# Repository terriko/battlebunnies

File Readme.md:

# Battle bunnies!

This is a goofy little side project that involves making a little electronic
bunny game in the name of learning a bit more about electronic badge design.

## How the game is played

Battle bunnies is meant to be a simple electronic game.  Each participant
gets their own bunny.  The bunnies have IR on one side of the PCB.
Participants line up their IR with the IR of another bunny and both hit the
"fight" button.  The bunnies each "roll" a random number 1-6 which is shown
on one ear and transmit that number to the other bunny.  The bunny with the
highest number gains a level.  In the case of a tie, both bunnies gain a
level (because why not?).  The levels are updated on the other ear.
Depending on how slow we want the level process to be, losing bunnies might
lose a level.

The "magic" button is an easter egg that can be activated when bunnies reach
max level.

## Bunny design

These are all early drafts which I'm sure we'll change.

### PCB outline

### Silkscreen bunny

### Explanation of what components go where

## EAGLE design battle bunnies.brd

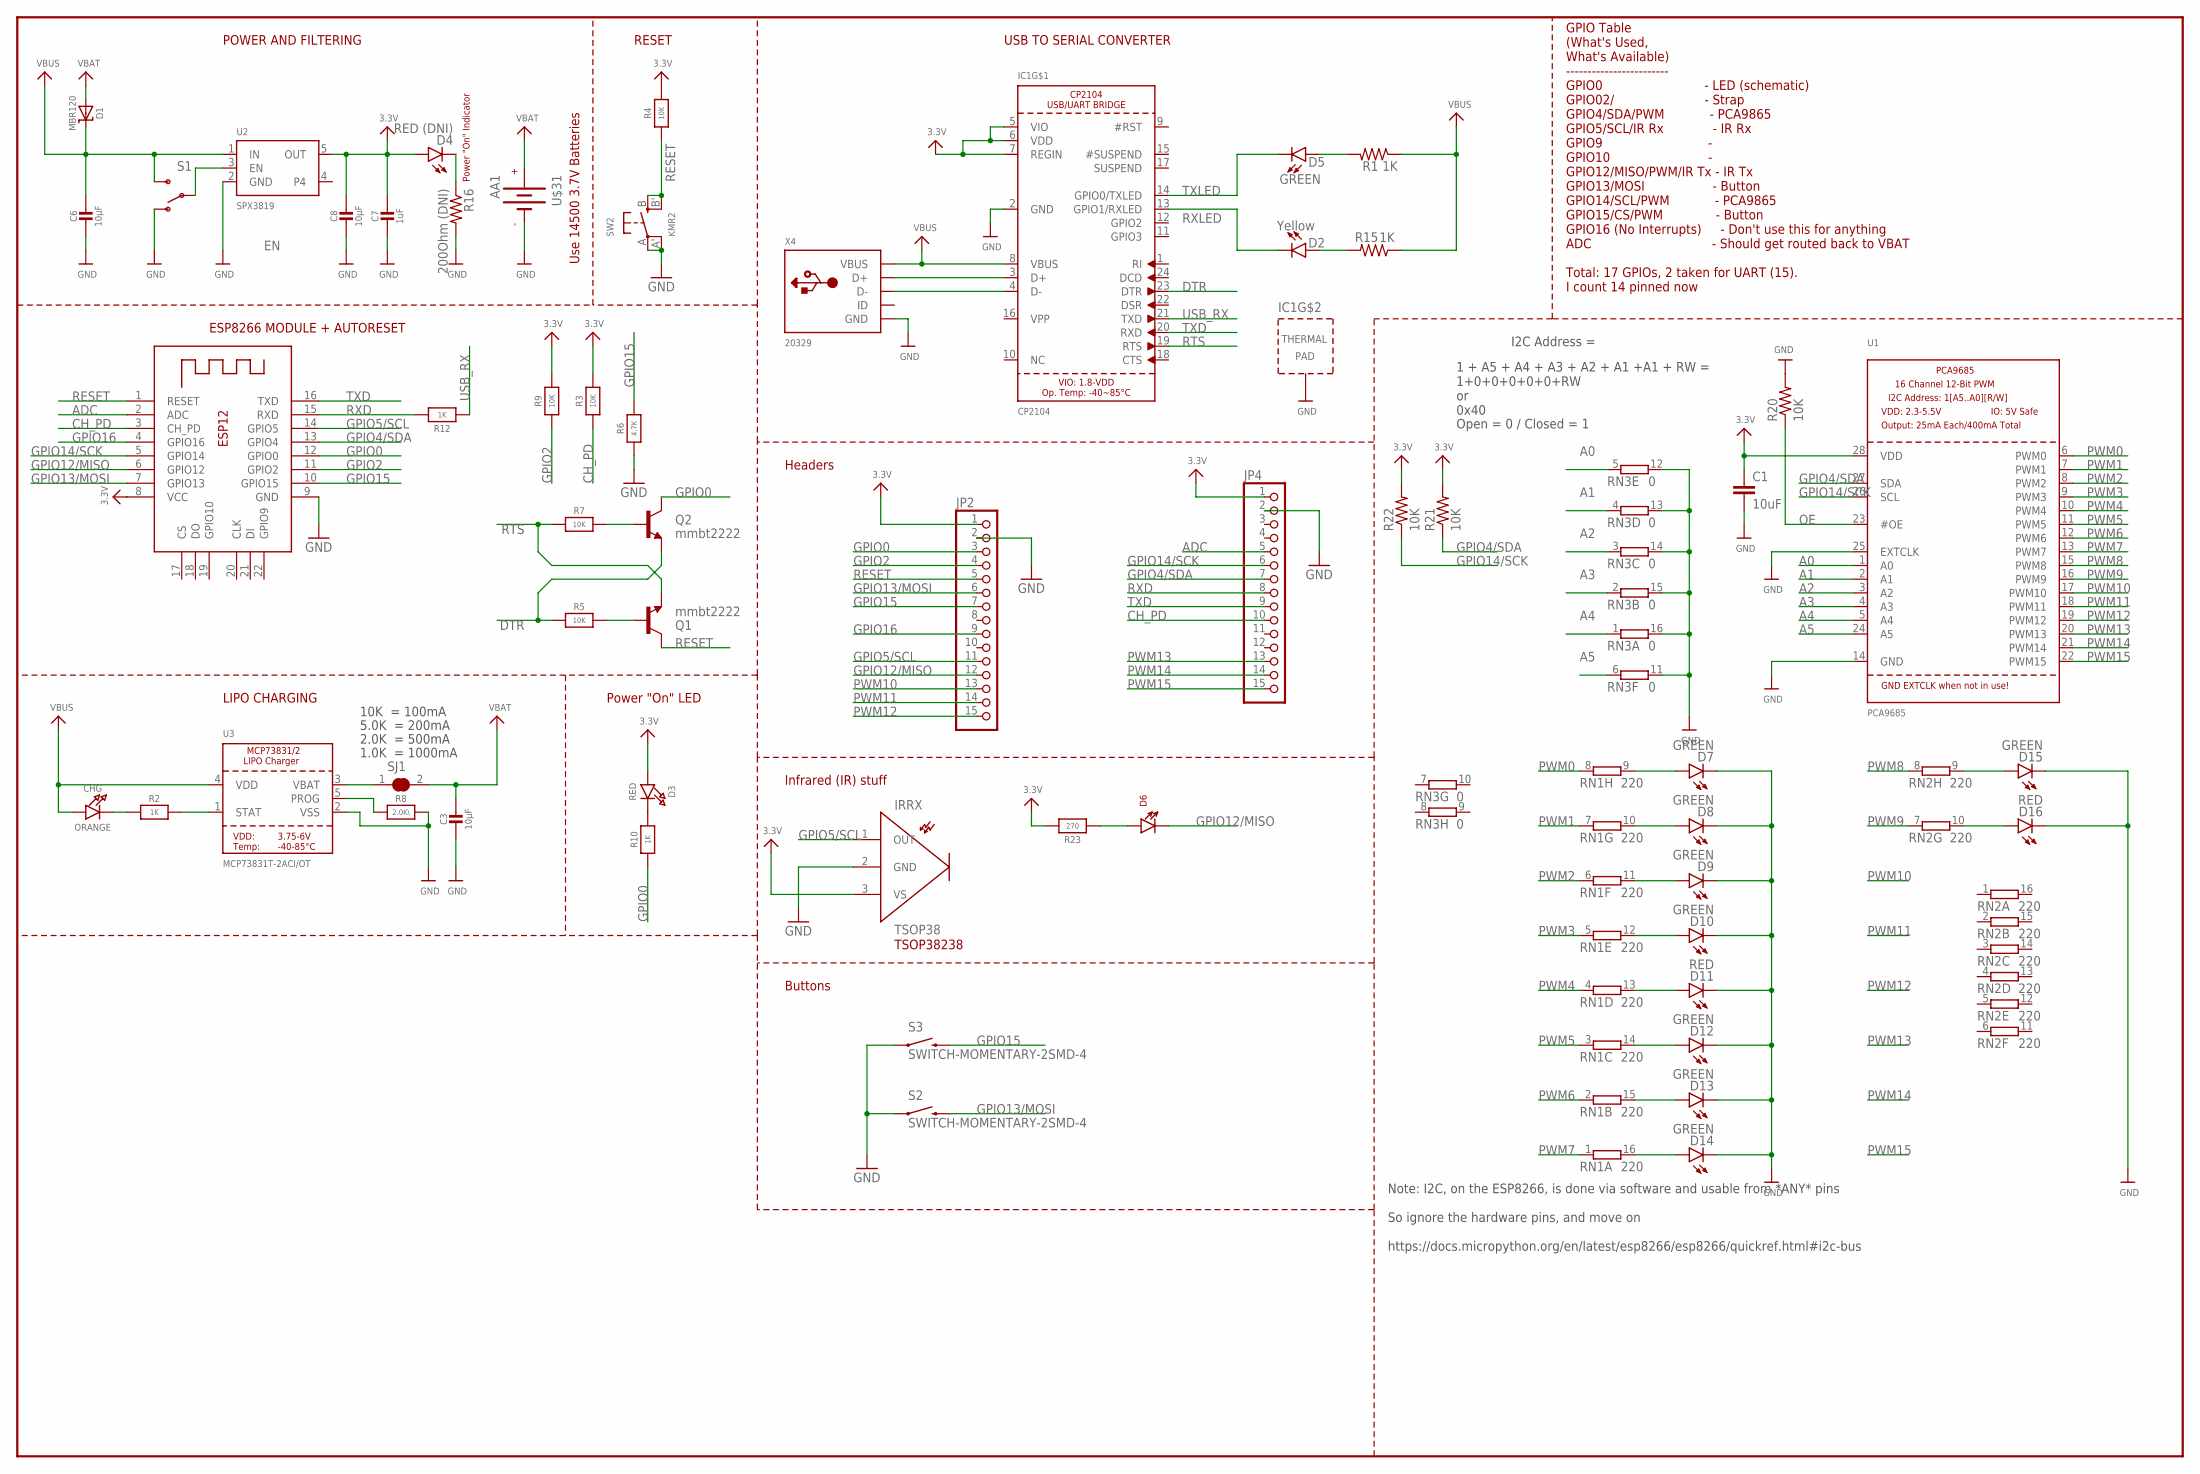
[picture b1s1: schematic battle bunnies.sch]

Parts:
C1: 10uF; 0805-CAP
C3, C6, C8: 10µF; 0805-NO
C7: 1uF; 0603-NO
CHG: ORANGE; CHIPLED_0805_NOOUTLINE
D1: MBR120; SOD-123
D2: Yellow; LED-0603
D3: RED; CHIPLED_0805_NOOUTLINE
D4: RED (DNI); LED-0603
D5, D7, D8, D9, D10, D12, D13, D14, D15: GREEN; LED-0603
D6: LTE-302
D11, D16: RED; LED-0603
IC1: CP2104; QFN24_4MM_SMSC
IRRX: TSOP38
JP2, JP4: PINHD-1X15; 1X15
Q1, Q2: mmbt2222; SOT23-3
R1, R15: 1K; 0603-RES
R2, R10: 1K; 0603-NO
R3, R4, R5, R9: 10K; 0603-NO
R6: 4.7K; 0603-NO
R7: 10K; _0603MP
R8: 2.0K\; 0603-NO
R12: 1K; _0603MP
R16: 200Ohm (DNI); 0603-RES
R20, R21, R22: 10K; 0805
R23: 270; 0603-NO
RN1, RN2: 220; EXB2HV
RN3: 0; EXB2HV
S1: SWITCH-SPDT-SMD-A; SWITCH-SPST-SMD-A
S2, S3: SWITCH-MOMENTARY-2SMD-4; TACTILE_SWITCH_TALL
SJ1: SOLDERJUMPER_CLOSED; SOLDERJUMPER_CLOSEDWIRE@1
SW2: KMR2; BTN_KMR2_4.6X2.8
U1: PCA9685; TSSOP28
U2: SPX3819; SOT23-5
U3: MCP73831T-2ACI/OT; SOT23-5
U$31: AA1
X2: ESP-12; ESP-12E
X4: 20329; 4UCONN_20329_V2

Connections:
3.3V: C1.1, C7.1, C8.1, D3.A, D4.A, IC1.5 (VIO), IC1.6 (VDD), IC1.7 (REGIN), IRRX.3 (VS), JP2.1, JP4.1, R1.1, R3.2, R4.2, R9.2, R15.1, R21.2, R22.2, R23.2, U1.28 (VDD), U2.5 (OUT), X2.8 (VCC)
A0: RN3.5 (1), U1.1 (A0)
A1: RN3.4 (1), U1.2 (A1)
A2: RN3.3 (1), U1.3 (A2)
A3: RN3.2 (1), U1.4 (A3)
A4: RN3.1, U1.5 (A4)
A5: RN3.6 (1), U1.24 (A5)
ADC: JP4.5, X2.2 (ADC)
CH_PD: JP4.10, R3.1, X2.3 (CH_PD)
DTR: IC1.23 (DTR), Q2.2 (E), R5.1
EN: S1.2, U2.3 (EN)
GND: C1.2, C3.2, C6.2, C7.2, C8.2, D7.C, D8.C, D9.C, D10.C, D11.C, D12.C, D13.C, D14.C, D15.C, D16.C, IC1.2 (GND), IC1.THERM (TP), IRRX.2 (GND), JP2.2, JP4.2, R6.1, R8.2, R16.2, R20.2, RN3.11 (2), RN3.12 (2), RN3.13 (2), RN3.14 (2), RN3.15 (2), RN3.16 (2), S1.1 (O), S2.A2 (1), S3.A2 (1), SW2.A, SW2.A' (P1), U1.14 (GND), U1.25 (EXTCLK), U2.2 (GND), U3.2 (VSS), U$31.NEG (-), X2.9 (GND), X4.BASE@1 (GND), X4.BASE@2 (GND), X4.GND, X4.SPRT@1 (GND), X4.SPRT@2 (GND), X4.SPRT@3 (GND), X4.SPRT@4 (GND)
GPIO0: JP2.3, Q2.3 (C), R10.1, X2.12 (GPIO0)
GPIO2: JP2.4, R9.1, X2.11 (GPIO2)
GPIO4/SDA: JP4.7, R21.1, U1.27 (SDA), X2.13 (GPIO4)
GPIO5/SCL: IRRX.1 (OUT), JP2.11, X2.14 (GPIO5)
GPIO12/MISO: D6.C, JP2.12, X2.6 (GPIO12)
GPIO13/MOSI: JP2.6, S2.B2 (2), X2.7 (GPIO13)
GPIO14/SCK: JP4.6, R22.1, U1.26 (SCL), X2.5 (GPIO14)
GPIO15: JP2.7, R6.2, S3.B2 (2), X2.10 (GPIO15)
GPIO16: JP2.9, X2.4 (GPIO16)
unnamed: CHG.C, R2.1
unnamed: R8.1, U3.5 (PROG)
unnamed: R2.2, U3.1 (STAT)
unnamed: D4.C, R16.1
unnamed: D3.C, R10.2
unnamed: D5.A, R1.2
unnamed: SJ1.1, U3.3 (VBAT)
unnamed: D2.A, R15.2
unnamed: Q1.1 (B), R5.2
unnamed: Q2.1 (B), R7.2
unnamed: D6.A, R23.1
unnamed: D13.A, RN1.15 (2)
unnamed: D14.A, RN1.16 (2)
unnamed: D12.A, RN1.14 (2)
unnamed: D11.A, RN1.13 (2)
unnamed: D10.A, RN1.12 (2)
unnamed: D9.A, RN1.11 (2)
unnamed: D8.A, RN1.10 (2)
unnamed: D7.A, RN1.9 (2)
unnamed: D15.A, RN2.9 (2)
unnamed: D16.A, RN2.10 (2)
OE: R20.1, U1.23 (#OE)
PWM0: RN1.8 (1), U1.6 (PWM0)
PWM1: RN1.7 (1), U1.7 (PWM1)
PWM2: RN1.6 (1), U1.8 (PWM2)
PWM3: RN1.5 (1), U1.9 (PWM3)
PWM4: RN1.4 (1), U1.10 (PWM4)
PWM5: RN1.3 (1), U1.11 (PWM5)
PWM6: RN1.2 (1), U1.12 (PWM6)
PWM7: RN1.1, U1.13 (PWM7)
PWM8: RN2.8 (1), U1.15 (PWM8)
PWM9: RN2.7 (1), U1.16 (PWM9)
PWM10: JP2.13, U1.17 (PWM10)
PWM11: JP2.14, U1.18 (PWM11)
PWM12: JP2.15, U1.19 (PWM12)
PWM13: JP4.13, U1.20 (PWM13)
PWM14: JP4.14, U1.21 (PWM14)
PWM15: JP4.15, U1.22 (PWM15)
RESET: JP2.5, Q1.3 (C), R4.1, SW2.B (S), SW2.B' (S1), X2.1 (RESET)
RTS: IC1.19 (RTS), Q1.2 (E), R7.1
RXD: JP4.8, R12.2, X2.15 (RXD)
RXLED: D2.C, IC1.13 (GPIO1/RXLED)
TXD: IC1.20 (RXD), JP4.9, X2.16 (TXD)
TXLED: D5.C, IC1.14 (GPIO0/TXLED)
USBD_N: IC1.4 (D-), X4.D-
USBD_P: IC1.3 (D+), X4.D+
USB_RX: IC1.21 (TXD), R12.1
VBAT: C3.1, D1.A, SJ1.2, U$31.POS (+)
VBUS: C6.1, CHG.A, D1.C, IC1.8 (VBUS), S1.3 (S), U2.1 (IN), U3.4 (VDD), X4.VBUS

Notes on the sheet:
POWER AND FILTERING
RESET
10K = 100mA
5.0K = 200mA
2.0K = 500mA
1.0K = 1000mA
USB TO SERIAL CONVERTER
LIPO CHARGING
Power "On" LED
ESP8266 MODULE + AUTORESET
Power "On" Indicator
GPIO Table (What's Used, What's Available) ------------------------ GPIO0 - LED (schematic) GPIO02/ - Strap GPIO4/SDA/PWM - PCA9865 GPIO5/SCL/IR Rx - IR Rx GPIO9 - GPIO10 - GPIO12/MISO/PWM/IR Tx - IR Tx GPIO13/MOSI - Button GPIO14/SCL/PWM - PCA9865 GPIO15/CS/PWM - Button GPIO16 (No Interrupts) - Do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
1 + A5 + A4 + A3 + A2 + A1 +A1 + RW = 1+0+0+0+0+0+RW or 0x40
I2C Address =
Open = 0 / Closed = 1
Note: I2C, on the ESP8266, is done via software and usable from *ANY* pins So ignore the hardware pins, and move on https://docs.micropython.org/en/latest/esp8266/esp8266/quickref.html#i2c-bus
Headers
Infrared (IR) stuff
TSOP38238
Buttons
Use 14500 3.7V Batteries

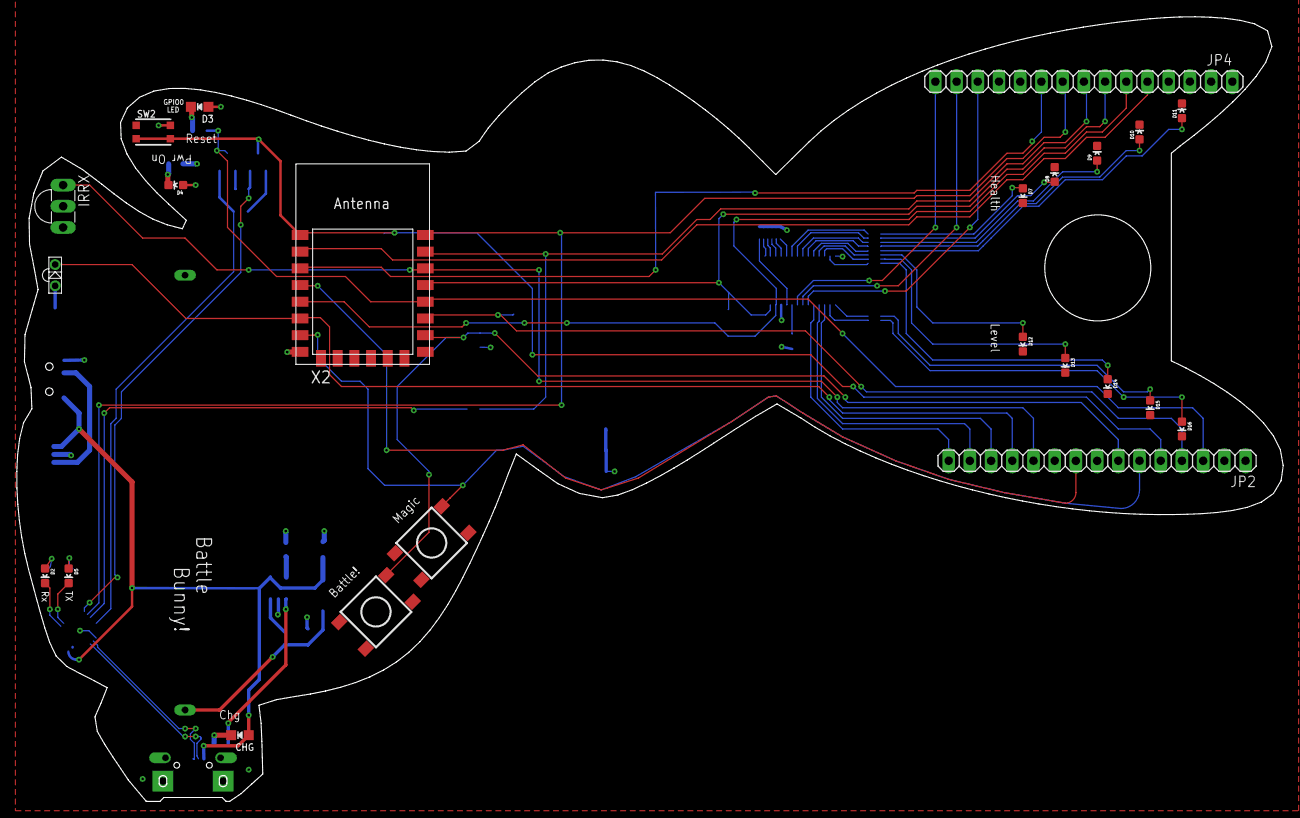
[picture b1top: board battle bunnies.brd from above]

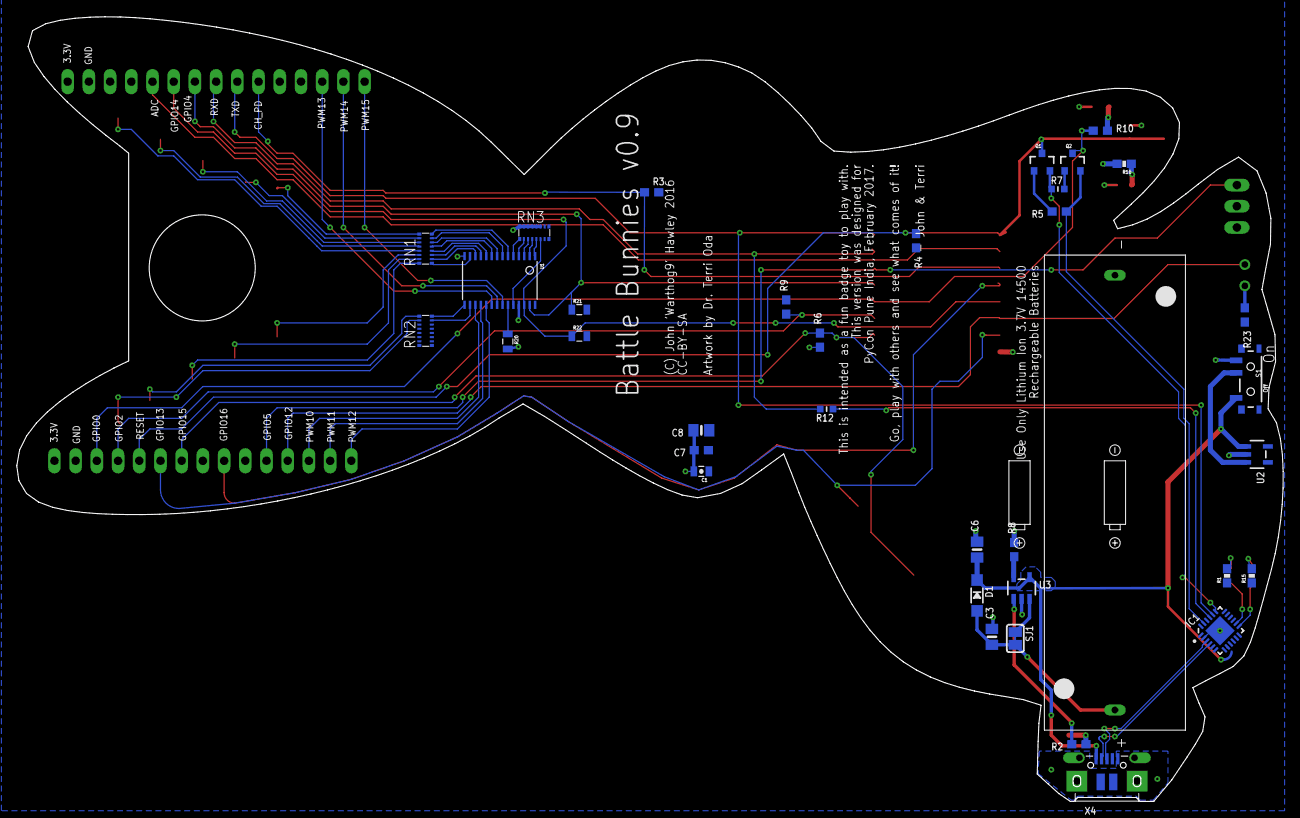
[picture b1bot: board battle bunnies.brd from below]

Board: 2 copper layers, 151.7 x 94.0 mm, 59 parts (36 on the bottom side), 70 nets.

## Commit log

2016-11-03 Design scratchpad
2016-11-03 Some additional variants
2016-11-03 Outline version
2016-11-03 Adding roughs based on my whiteboard sketches
2016-11-03 Explanation with png pictures for easier viewing
2016-11-03 resized for easier viewing
2017-01-02 Adding Board Schematic, Layout, & additional files for design
2017-01-25 Fixing Power LED
    Right now the 'Power LED' is run from Ground to... Ground, so it's
    not exactly going to work 'right'. When moving things around in
    Eagle it didn't attach properly to the 3.3V line on the schematic
    and so was left dangling, despite it being connected.
    This, thankfully, doesn't affect the boards except cause a little
    bit of build waste. This is fixed now, though it'll likely get
2017-01-25 Updating GPIO Table to actually be correct with the schematic
2017-01-25 Flipping GPIO16 with GPIO15 on the 'Battle' Button
    GPIO16 *APPARENTLY* doesn't actually have hard interrupt
    support, which makes it slightly obnoxious for the 'battle'
    button, which should be there to wake the bunny from a sleep
    state, or get it to do something.
2017-01-25 Marking the "Power On" LEDs as DNI
    They aren't needed and adding them is more a debugging
    nicety vs. a critical need.
2017-01-25 Marking On/Off on the main power switch
2017-02-25 Adding warning / notice about battery to be used
2017-02-25 Fixing the trace that ran through the exposed ear
2017-02-25 Updating the GPIO table
    Turns out 16 is really unusable for anything even
    remotely useful. (case in point it has no pull-up available)
2017-02-25 Removing extraneous via on GPIO14/SCK
2017-02-25 Fixing the USB impedance issue (moving USB chip)
    This is a pretty big change as I'm moving a bunch of stuff around
    which obviously causes it's own issues, but this should be ok
2017-02-25 Adding some clearances around lines passing through the ESP8266
    This *SHOULDN'T* be the problem with the IR RX but it can't hurt
2017-02-25 Cleaning up various DRC errors (mostly stop mask issues)
    This should also make the general text easier to read
2017-02-25 Adding values to the RNs that were missing
2017-02-25 Adding back in the lanyard hole
    Oops
2017-02-25 Smashing RN3 to deal with DRC errors
2017-02-25 Adding a PDF version of the schematic
    I don't garauntee it to be up to date with the actual schematic
    so take it with a grain of salt

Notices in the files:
battle bunnies.brd:
CC-BY-SA
parts and their libraries:
SparkFun-Capacitors: Licensing: Creative Commons ShareAlike 4.0 International - https://creativecommons.org/licenses/by-sa/4.0
microbuilder: This work is placed in the public domain, and may be freely used for commercial and non-commercial work with the following conditions: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
